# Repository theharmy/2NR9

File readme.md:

# TwoNr9 (2NR9) is a minimalistic ergonomic 20% Keyboard. 

[Pictures by Purox/Nex](https://ncxy.de/)

## Files In this Repo 
- The PROD files as ZIP as well as a folder, the Kicad PCB File 
- CASE (To-Do)

## Features: 
- 18 Keys with an Minimalistic  Design and Case
- The Case offers hidden Magnet sockets for Magsafe Compability
- Switches: Choc V2 Hotswap 
- MCU: N!N (or Clones)
- battery: 301230 3.7V 110mAh Lipo Battery
  - only this one works due to size Constraints.
- Designed Together with [Purox/Nex](https://ncxy.de/)

### Note 
~~BOTTOM MIDDLE FINGER AND THE PINKY NEED A BODGE WIRE DUE TO WRONGLY FLIPPED HOTSWAP SOCKETS.~~

The Pads for the pinky and bottom middle finger might look odd due to small changes in size, that prevents a bodge wire and should not influence the functionality. 

## ZMK Config: 
- There is a [Blanc Version of the Config](https://github.com/theharmy/zmk-config-twonr9--blank)
- My personal [Config](https://github.com/theharmy/zmk-config), (AI CODE WARNING)
	- with [SRHT by Apfel](https://codeberg.org/apfel)  (A Germlish 2Alpha Layout with Bigrams)
	- and many features of [Urob's ZMK Config](https://github.com/urob/zmk-config) 

### Acknowledgements
- Big Thanks and Much love to 
	- [Purox/Nex](https://ncxy.de/) for a lot of test-printing with me, PCB Design-Support and Feedback.
		- Their: 
			- [Blog](https://ncxy.de/) 
			- [Keyboard Work](https://git.clacktal.es/purox)
			- [Github](https://github.com/ThePurox)
	- Kilipan/Apfel for Getting me Into the 20% Madness, Creation of the SRHT Layout, Patience and Input
		- their:
			- [Codeberg](https://codeberg.org/apfel), for general projects
			- [clacktal.es](https://git.clacktal.es/apfel), for keyboard-related things

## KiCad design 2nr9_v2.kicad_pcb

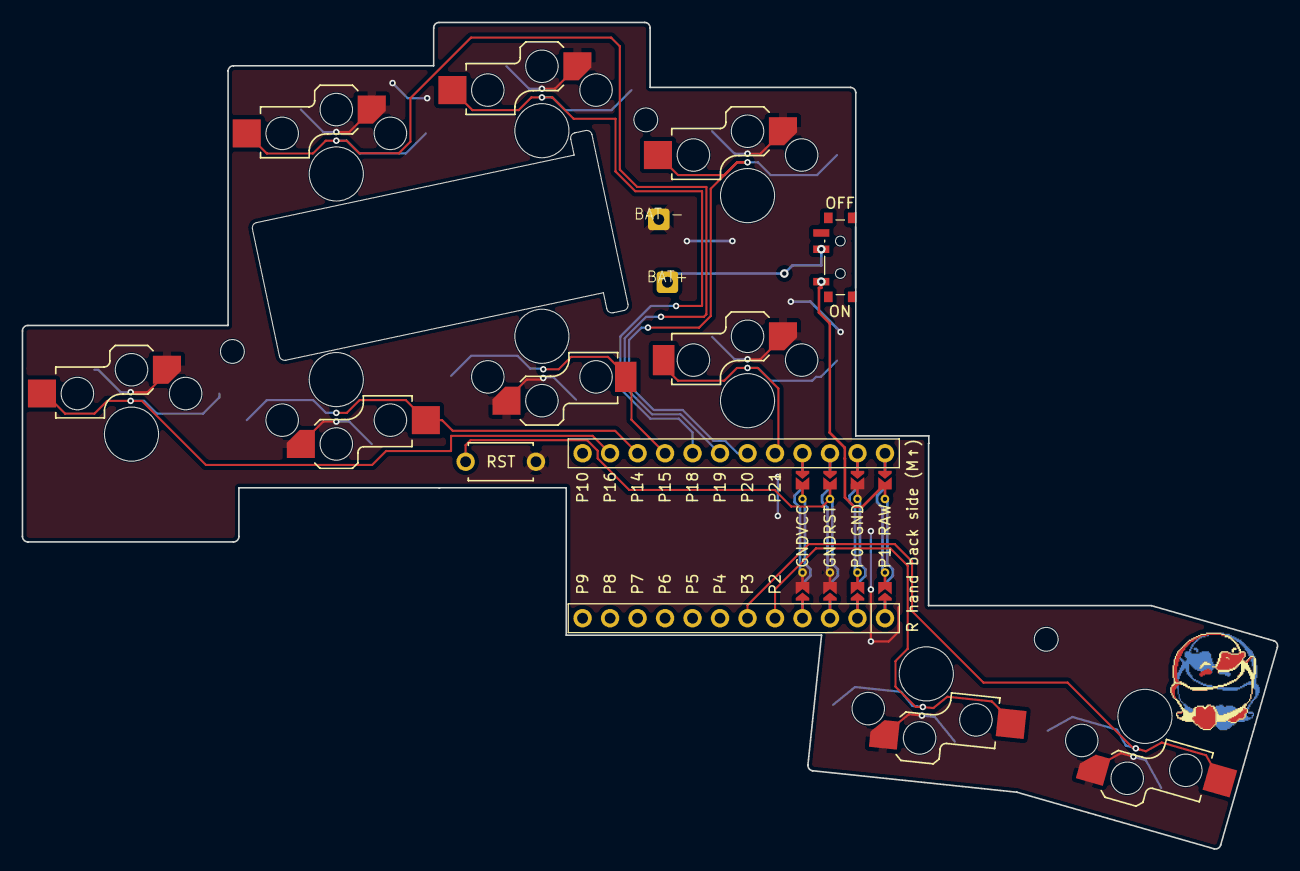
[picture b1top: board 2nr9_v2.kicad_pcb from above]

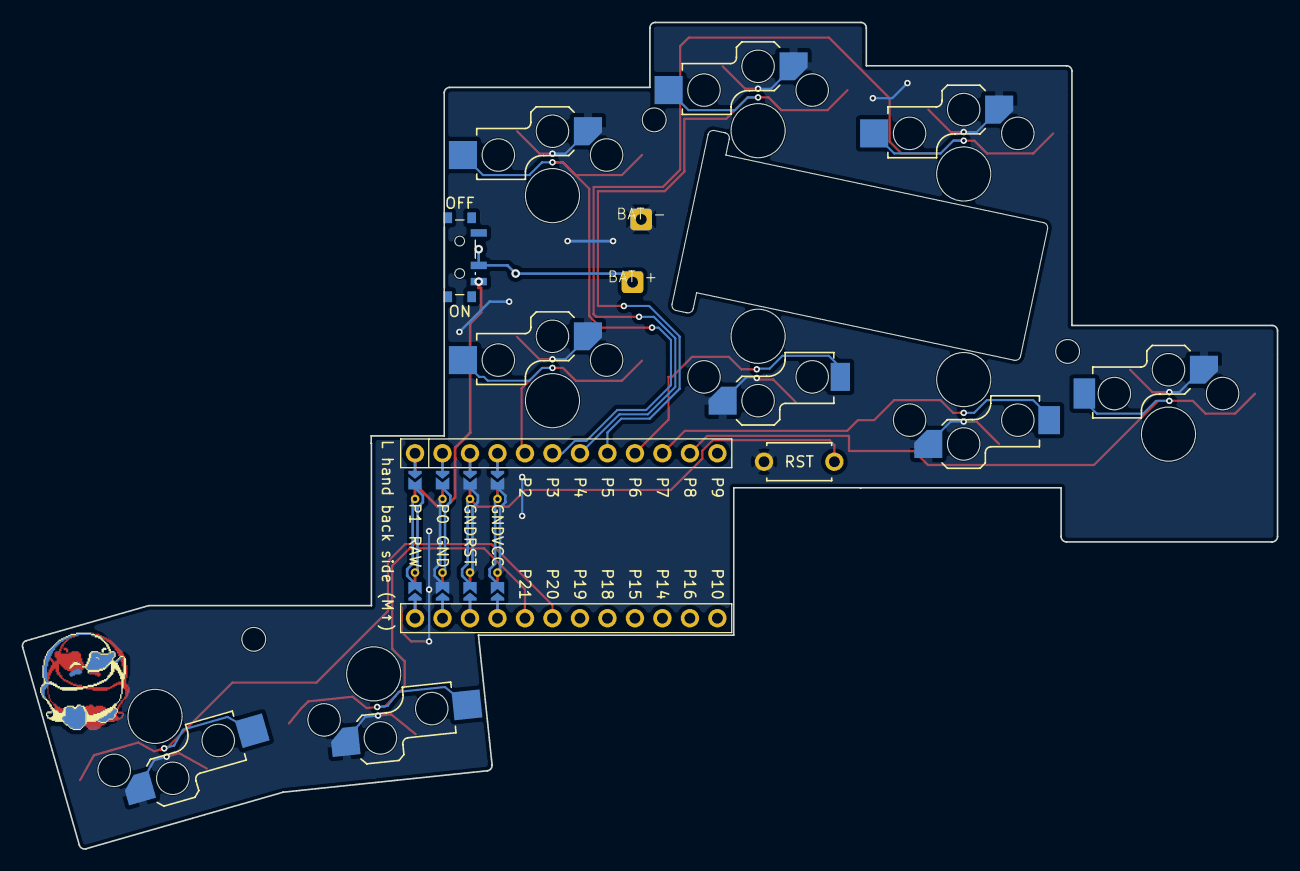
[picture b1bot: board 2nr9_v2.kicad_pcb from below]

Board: 2 copper layers, 116.0 x 76.4 mm, 19 parts (13 on the bottom side), 13 nets.

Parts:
BAT +: BatteryCablePad
BAT -: BatteryCablePad
BAT -#2: BatteryCablePad
BAT+: BatteryCablePad
MCU1: mcu_nice_nano
MH1, MH2, MH3: mounting_hole_npth
PWR1: power_switch_smd_side
RST1: reset_switch_tht_top
S1, S2, S3, S4, S5, S6, S7, S8, S9: switch_choc_v1_v2

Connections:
BAT_P: BAT +.1, BAT+.1, PWR1.2
GND: BAT -.1, BAT -#2.1, MCU1.103, MCU1.104, MCU1.123, RST1.1, S1.1, S2.1, S3.1, S4.1, S5.1, S6.1, S7.1, S8.1, S9.1
P2: MCU1.5, S8.2
P3: MCU1.6, S9.2
P14: MCU1.15, S2.2
P15: MCU1.16, S4.2
P16: MCU1.14, S1.2
P18: MCU1.17, S5.2
P19: MCU1.18, S3.2
P20: MCU1.19, S7.2
P21: MCU1.20, S6.2
RAW: MCU1.124, PWR1.1, PWR1.3
RST: MCU1.122, RST1.2
